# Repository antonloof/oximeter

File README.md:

# oximeter
a oximeter, used as demo project for ETA-dagen 2021. Actual hw is not in this repo, just test hw

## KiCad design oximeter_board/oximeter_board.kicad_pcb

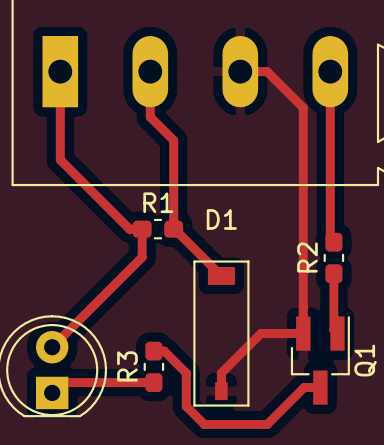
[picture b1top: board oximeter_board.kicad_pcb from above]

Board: 2 copper layers, 7 parts (0 on the bottom side), 7 nets.

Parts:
D1: D_Photo; sfh-2440-l
D2: LED; LED_D5.0mm
J1: Conn_01x04; TerminalBlock_Altech_AK300-4_P5.00mm
Q1: Q_NMOS_GSD; SOT-23_Handsoldering
R1, R2, R3: R_Small; R_0603_1608Metric_Pad1.05x0.95mm_HandSolder

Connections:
+3V3: D2.2, J1.1, R1.1
/led_ctrl: J1.4, R2.2
/photo_diode: D1.1, J1.2, R1.2
GND: D1.2, J1.3, Q1.2
unnamed: D2.1, R3.1
unnamed: Q1.1, R2.1
unnamed: Q1.3, R3.2

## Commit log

2021-08-22 Initial commit
    Includes
    * test board
    * pico sw for initial test
    * pycom sw for second test
    * my hatred towards pymakr for vscode
2021-08-22 Filter design done
2021-08-23 IT WORKSSSSS
2021-08-24 Add raw data
2021-08-24 Update filter values and prominence
2021-08-24 Turns out 32 bit floats cant do the 2nd order filter
2021-08-24 Turns out reality is difficult
2021-08-25 Add led ctrl
